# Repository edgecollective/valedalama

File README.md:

# valedalama

https://github.com/the-louie/arduino-lmic/tree/louie-add-naive-eu433-support

bossac -p /dev/cu.usbmodem14301 -e -w -v -R adafruit-circuitpython-boardname-version.bin

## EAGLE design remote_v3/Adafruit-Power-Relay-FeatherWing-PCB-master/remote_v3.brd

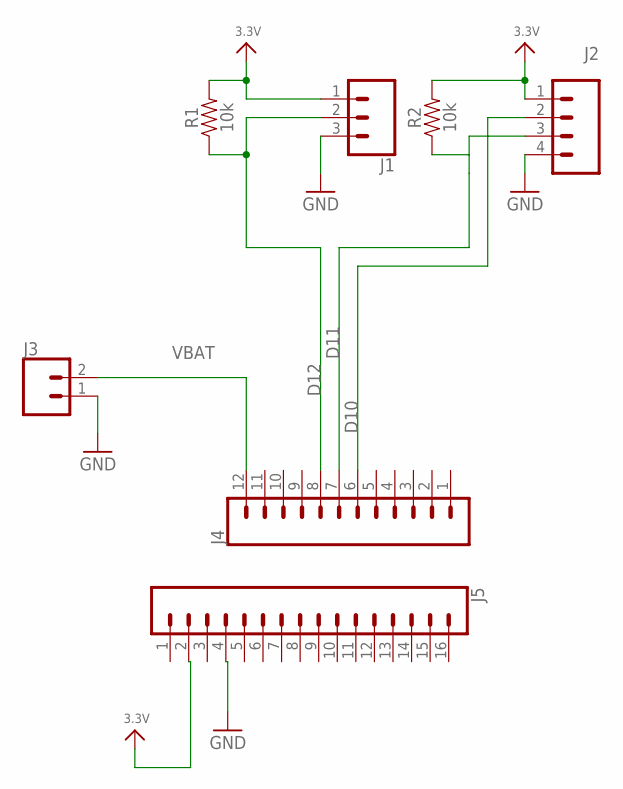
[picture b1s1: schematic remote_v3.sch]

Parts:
J1: CONN_03SCREW; SCREWTERMINAL-3.5MM-3
J2: CONN_04SCREW; SCREWTERMINAL-3.5MM-4
J3: CONN_023.5MM; SCREWTERMINAL-3.5MM-2
J4: CONN_12; 1X12
J5: CONN_16; 1X16
R1, R2: 10k; AXIAL-0.3

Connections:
3.3V: J1.1, J2.1, J5.2, R1.P$2 (2), R2.P$2 (2)
D10: J2.2, J4.6
D11: J2.3, J4.7, R2.P$1 (1)
D12: J1.2, J4.8, R1.P$1 (1)
GND: J1.3, J2.4, J3.1, J5.4
VBAT: J3.2, J4.12

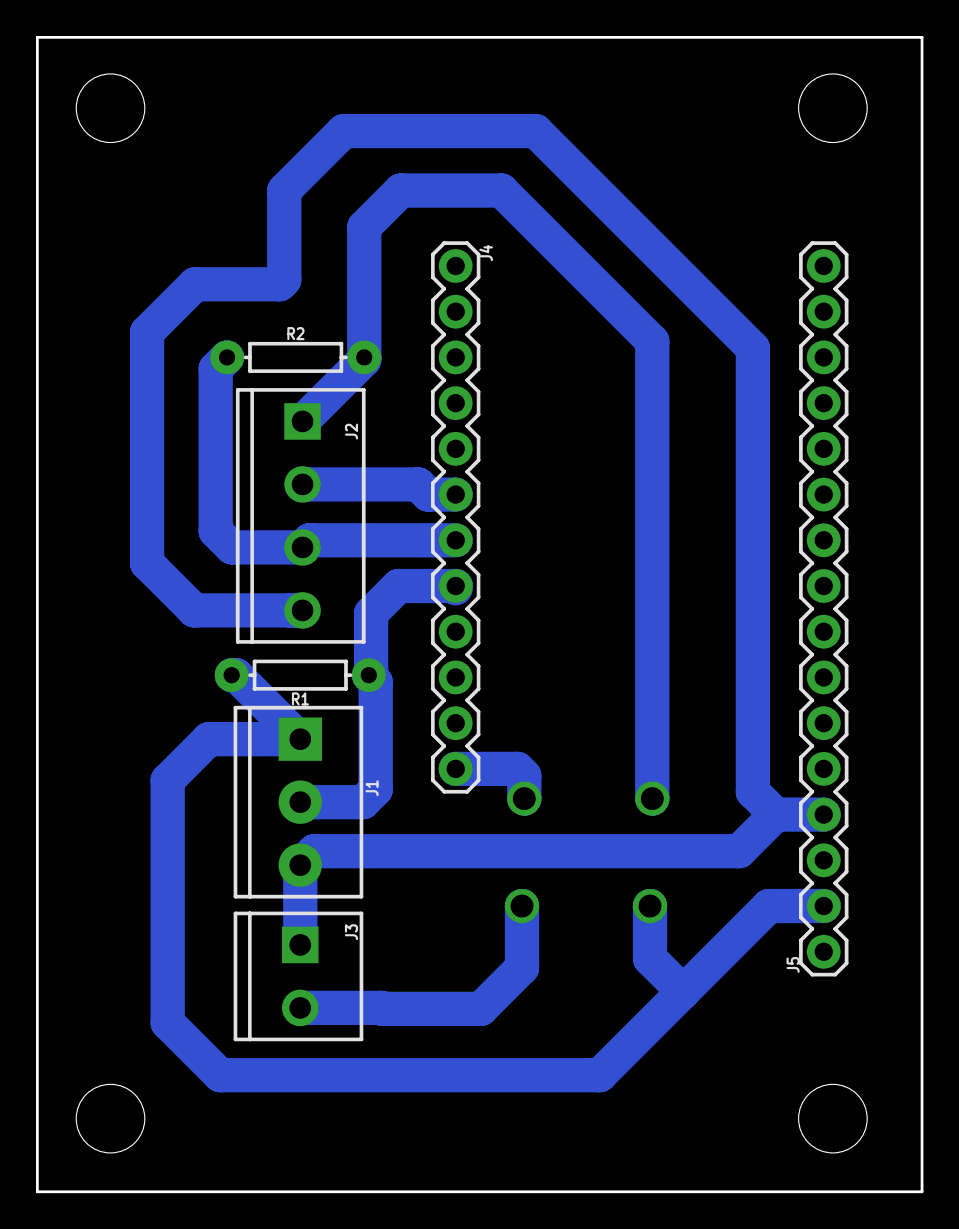
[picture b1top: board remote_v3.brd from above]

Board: 2 copper layers, 49.1 x 64.1 mm, 7 parts (0 on the bottom side), 6 nets.

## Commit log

2020-11-24 re-initialize StaticJsonDocument every loop, to avoid memory leaks

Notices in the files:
parts and their libraries:
SparkFun-Connectors: Licensing: Creative Commons ShareAlike 4.0 International - https://creativecommons.org/licenses/by-sa/4.0
microbuilder: This work is placed in the public domain, and may be freely used for commercial and non-commercial work with the following conditions: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
